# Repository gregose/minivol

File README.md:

# minivol

This is modifications and improvements to the firmware for the MiniVol PGA2320 volume control project. The original project is hosted at http://audio.gotroot.ca/minivol/.

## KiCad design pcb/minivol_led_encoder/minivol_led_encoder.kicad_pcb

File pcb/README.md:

Kicad (nightly) project for front panel PCB w/ encoder breakout, shift register and LEDs.

**:warning: Warning! The sn74hc595 was placed on the incorrect side of the board! You will have to flip the pins to the other side of the IC for it to be mounted on the non-copper side**

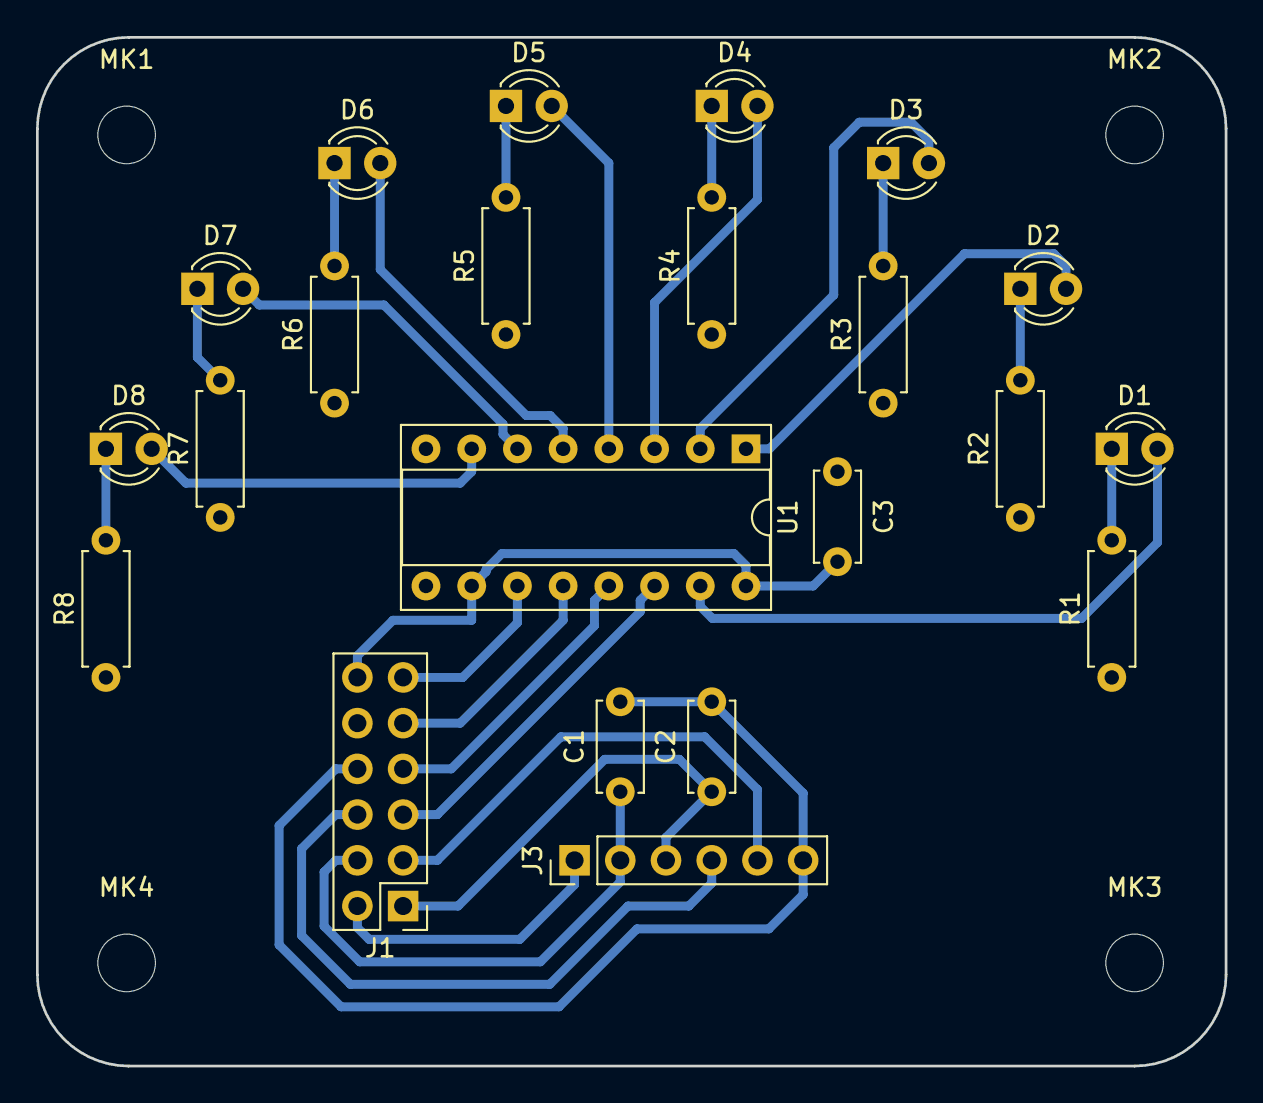
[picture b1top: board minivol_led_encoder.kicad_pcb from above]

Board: 2 copper layers, 66.0 x 57.2 mm, 26 parts (0 on the bottom side), 27 nets.

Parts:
C1, C2, C3: 0.1uF; C_Disc_D5.0mm_W2.5mm_P5.00mm
D1, D2, D3, D4, D5, D6, D7, D8: LED_Small; LED_D3.0mm
J1: Encoder and SPI input; Pin_Header_Straight_2x06_Pitch2.54mm
J3: Encoder output; Pin_Header_Straight_1x06_Pitch2.54mm
MK1, MK2, MK3, MK4: Mounting_Hole; MountingHole_3.2mm_M3
R1, R2, R3, R4, R5, R6, R7, R8: 560R; R_Axial_DIN0207_L6.3mm_D2.5mm_P7.62mm_Horizontal
U1: 74HC595; DIP-16_W7.62mm_Socket

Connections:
+3V3: J1.2, J3.1
+5V: C3.2, J1.12, U1.10, U1.16
BTN_IN: J1.6, J3.4
BTN_OUT: J1.3, J3.5
CLK: J1.11, U1.11
ENC_A: C1.1, J1.4, J3.2
ENC_B: C2.1, J1.1, J3.3
GND: C3.1, J1.7, J1.10, R1.1, R2.1, R3.1, R4.1, R5.1, R6.1, R7.1, R8.1, U1.8, U1.13
GNDA: C1.2, C2.2, J1.8, J3.6
MOSI: J1.5, U1.14
unnamed: D1.1, R1.2
unnamed: D1.2, U1.15
unnamed: D2.1, R2.2
unnamed: D2.2, U1.1
unnamed: D3.1, R3.2
unnamed: D3.2, U1.2
unnamed: D4.1, R4.2
unnamed: D4.2, U1.3
unnamed: D5.1, R5.2
unnamed: D5.2, U1.4
unnamed: D6.1, R6.2
unnamed: D6.2, U1.5
unnamed: D7.1, R7.2
unnamed: D7.2, U1.6
unnamed: D8.1, R8.2
unnamed: D8.2, U1.7
SS: J1.9, U1.12

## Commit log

2017-04-01 intial import from http://audio.gotroot.ca/minivol/minivol-src-1.0.zip
2017-04-03 update gitignore
2017-04-03 Makefile and crlf cleanup
2017-04-12 Makefile and build fixes, add program-fuse target to makefile
2017-04-12 fix some compiler warnings
2018-01-14 initial support for sn74hc595 shift register
2018-01-14 add back enc lookup comment
2018-01-14 use ENC pin for shift CS, update shift reg w/ volume
2018-01-14 light sequential LEDs
2018-01-15 front panel pcb layout
2018-01-15 flat cam CNC jobs
2018-01-23 final update
2018-01-23 add pcb warning and readme
